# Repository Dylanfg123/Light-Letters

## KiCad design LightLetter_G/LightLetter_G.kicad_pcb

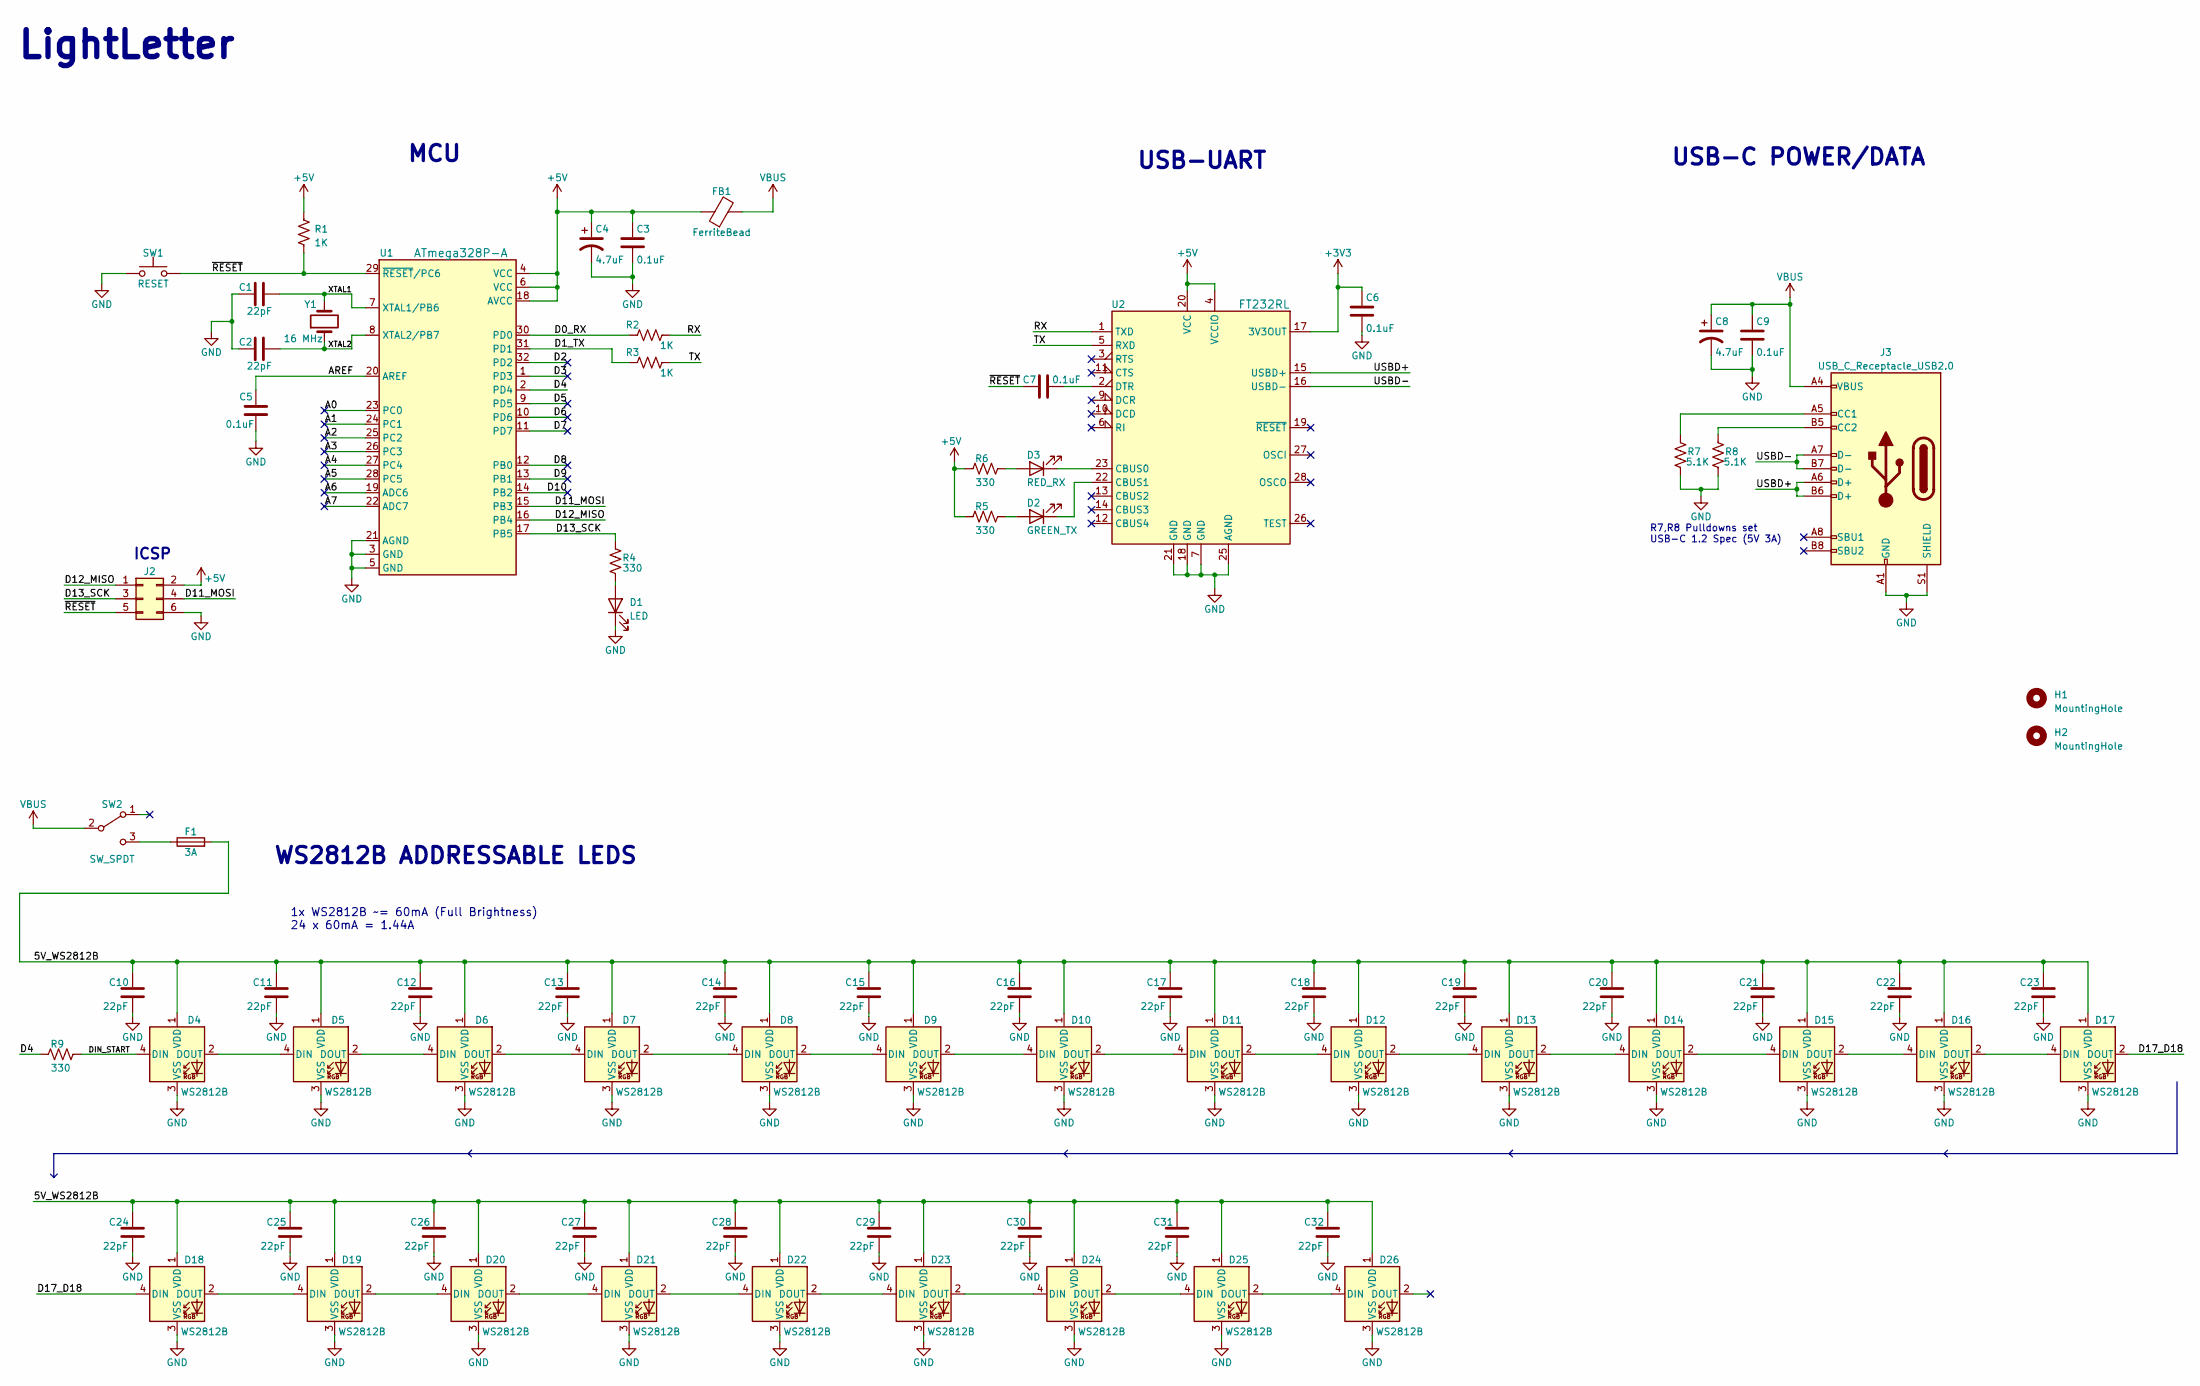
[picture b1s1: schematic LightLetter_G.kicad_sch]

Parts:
C1, C2, C10, C11, C12, C13, C14, C15, C16, C17, C18, C19, C20, C21, C22, C23, C24, C25, C26, C27, C28, C29, C30, C31, C32: 22pF; C_0603_1608Metric; Digikey# 478-KGM15ACG1H220JTCT-ND
C3, C5, C6, C7, C9: 0.1uF; C_0603_1608Metric; Digikey# 478-KGM15BR71H104KMCT-ND
C4, C8: 4.7uF; C_0603_1608Metric; Digikey# 490-12328-1-ND
D1: LED; LED_0603_1608Metric; Digikey# 160-1446-1-ND
D2: GREEN_TX; LED_0603_1608Metric; Digikey# 160-1446-1-ND
D3: RED_RX; LED_0603_1608Metric; Digikey# 160-1447-1-ND
D4, D5, D6, D7, D8, D9, D10, D11, D12, D13, D14, D15, D16, D17, D18, D19, D20, D21, D22, D23, D24, D25, D26: WS2812B; LED_WS2812B_PLCC4_5.0x5.0mm_P3.2mm; Digikey# 1568-COM-16347CT-ND
F1: 3A; Fuse_1206_3216Metric; Digikey# 507-1896-1-ND
FB1: FerriteBead; L_0603_1608Metric; Digikey# 240-2558-1-ND
H1, H2: MountingHole; MountingHole_3.2mm_M3
J2: Conn_02x03_Odd_Even; PinHeader_2x03_P1.27mm_Vertical_SMD; Digikey# SAM14930CT-ND
J3: USB_C_Receptacle_USB2.0; USB_C_Receptacle_GCT_USB4115-03-C; Digikey# 2073-USB4115-03-CCT-ND
R1, R2, R3: 1K; R_0603_1608Metric; Digikey# 311-1.00KHRCT-ND
R4, R5, R6, R9: 330; R_0603_1608Metric; Digikey# 118-CMP0603-FX-3300ELFCT-ND
R7, R8: 5.1K; R_0603_1608Metric; Digikey# RMCF0603FT5K10CT-ND
SW1: RESET; SW_Push_1P1T_NO_6x6mm_H9.5mm; Digikey# CKN10880CT-ND
SW2: SW_SPDT; SW_500ASSP1M6QE; Digikey# EG2483-ND
U1: ATmega328P-A; TQFP-32_7x7mm_P0.8mm; Digikey# ATMEGA328PB-AURCT-ND
U2: FT232RL; SSOP-28_5.3x10.2mm_P0.65mm; Digikey# 768-1007-1-ND
Y1: 16 MHz; XTAL_ABLS7M-16.000MHZ-B-2-T; Digikey# 535-13416-1-ND

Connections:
+3V3: C6.1, U2.17 (3V3OUT)
+5V: C3.1, C4.1, FB1.1, J2.2, R1.1, R5.2, R6.2, U1.4 (VCC), U1.6 (VCC), U1.18 (AVCC), U2.4 (VCCIO), U2.20 (VCC)
/5V_WS2812B: C10.2, C11.2, C12.2, C13.2, C14.2, C15.2, C16.2, C17.2, C18.2, C19.2, C20.2, C21.2, C22.2, C23.2, C24.2, C25.2, C26.2, C27.2, C28.2, C29.2, C30.2, C31.2, C32.2, D4.1 (VDD), D5.1 (VDD), D6.1 (VDD), D7.1 (VDD), D8.1 (VDD), D9.1 (VDD), D10.1 (VDD), D11.1 (VDD), D12.1 (VDD), D13.1 (VDD), D14.1 (VDD), D15.1 (VDD), D16.1 (VDD), D17.1 (VDD), D18.1 (VDD), D19.1 (VDD), D20.1 (VDD), D21.1 (VDD), D22.1 (VDD), D23.1 (VDD), D24.1 (VDD), D25.1 (VDD), D26.1 (VDD), F1.2
/A0: U1.23 (PC0)
/A1: U1.24 (PC1)
/A2: U1.25 (PC2)
/A3: U1.26 (PC3)
/A4: U1.27 (PC4)
/A5: U1.28 (PC5)
/A6: U1.19 (ADC6)
/A7: U1.22 (ADC7)
/AREF: C5.1, U1.20 (AREF)
/D0_RX: R2.1, U1.30 (PD0)
/D1_TX: R3.1, U1.31 (PD1)
/D2: U1.32 (PD2)
/D3: U1.1 (PD3)
/D4: R9.2, U1.2 (PD4)
/D5: U1.9 (PD5)
/D6: U1.10 (PD6)
/D7: U1.11 (PD7)
/D8: U1.12 (PB0)
/D9: U1.13 (PB1)
/D10: U1.14 (PB2)
/D11_MOSI: J2.4, U1.15 (PB3)
/D12_MISO: J2.1, U1.16 (PB4)
/D13_SCK: J2.3, R4.2, U1.17 (PB5)
/D17_D18: D17.2 (DOUT), D18.4 (DIN)
/DIN_START: D4.4 (DIN), R9.1
/RX: R2.2, U2.1 (TXD)
/TX: R3.2, U2.5 (RXD)
/USBD+: J3.A6 (D+), J3.B6 (D+), U2.15 (USBD+)
/USBD-: J3.A7 (D-), J3.B7 (D-), U2.16 (USBD-)
/XTAL1: C1.2, U1.7 (XTAL1/PB6), Y1.2
/XTAL2: C2.2, U1.8 (XTAL2/PB7), Y1.1
/~RESET: C7.1, J2.5, R1.2, SW1.2, U1.29 (~RESET/PC6)
GND: C1.1, C2.1, C3.2, C4.2, C5.2, C6.2, C8.2, C9.2, C10.1, C11.1, C12.1, C13.1, C14.1, C15.1, C16.1, C17.1, C18.1, C19.1, C20.1, C21.1, C22.1, C23.1, C24.1, C25.1, C26.1, C27.1, C28.1, C29.1, C30.1, C31.1, C32.1, D1.1 (K), D4.3 (VSS), D5.3 (VSS), D6.3 (VSS), D7.3 (VSS), D8.3 (VSS), D9.3 (VSS), D10.3 (VSS), D11.3 (VSS), D12.3 (VSS), D13.3 (VSS), D14.3 (VSS), D15.3 (VSS), D16.3 (VSS), D17.3 (VSS), D18.3 (VSS), D19.3 (VSS), D20.3 (VSS), D21.3 (VSS), D22.3 (VSS), D23.3 (VSS), D24.3 (VSS), D25.3 (VSS), D26.3 (VSS), J2.6, J3.A1 (GND), J3.A12 (GND), J3.B1 (GND), J3.B12 (GND), J3.S1 (SHIELD), R7.1, R8.1, SW1.1, U1.3 (GND), U1.5 (GND), U1.21 (AGND), U2.7 (GND), U2.18 (GND), U2.21 (GND), U2.25 (AGND)
unnamed: D1.2 (A), R4.1
unnamed: D2.2 (A), R5.1
unnamed: D2.1 (K), U2.22 (CBUS1)
unnamed: D3.2 (A), R6.1
unnamed: D3.1 (K), U2.23 (CBUS0)
unnamed: D4.2 (DOUT), D5.4 (DIN)
unnamed: D5.2 (DOUT), D6.4 (DIN)
unnamed: D6.2 (DOUT), D7.4 (DIN)
unnamed: D7.2 (DOUT), D8.4 (DIN)
unnamed: D8.2 (DOUT), D9.4 (DIN)
unnamed: D9.2 (DOUT), D10.4 (DIN)
unnamed: D10.2 (DOUT), D11.4 (DIN)
unnamed: D11.2 (DOUT), D12.4 (DIN)
unnamed: D12.2 (DOUT), D13.4 (DIN)
unnamed: D13.2 (DOUT), D14.4 (DIN)
unnamed: D14.2 (DOUT), D15.4 (DIN)
unnamed: D15.2 (DOUT), D16.4 (DIN)
unnamed: D16.2 (DOUT), D17.4 (DIN)
unnamed: D18.2 (DOUT), D19.4 (DIN)
unnamed: D19.2 (DOUT), D20.4 (DIN)
unnamed: D20.2 (DOUT), D21.4 (DIN)
unnamed: D21.2 (DOUT), D22.4 (DIN)
unnamed: D22.2 (DOUT), D23.4 (DIN)
unnamed: D23.2 (DOUT), D24.4 (DIN)
unnamed: D24.2 (DOUT), D25.4 (DIN)
unnamed: D25.2 (DOUT), D26.4 (DIN)
unnamed: J3.A5 (CC1), R7.2
unnamed: J3.B5 (CC2), R8.2
unnamed: F1.1, SW2.3 (C)
unnamed: C7.2, U2.2 (DTR)
VBUS: C8.1, C9.1, FB1.2, J3.A4 (VBUS), J3.A9 (VBUS), J3.B4 (VBUS), J3.B9 (VBUS), SW2.2 (B)

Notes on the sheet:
R7,R8 Pulldowns set USB-C 1.2 Spec (5V 3A)
USB-C POWER/DATA
WS2812B ADDRESSABLE LEDS
MCU
1x WS2812B ~= 60mA (Full Brightness) 24 x 60mA = 1.44A
LightLetter
USB-UART
ICSP

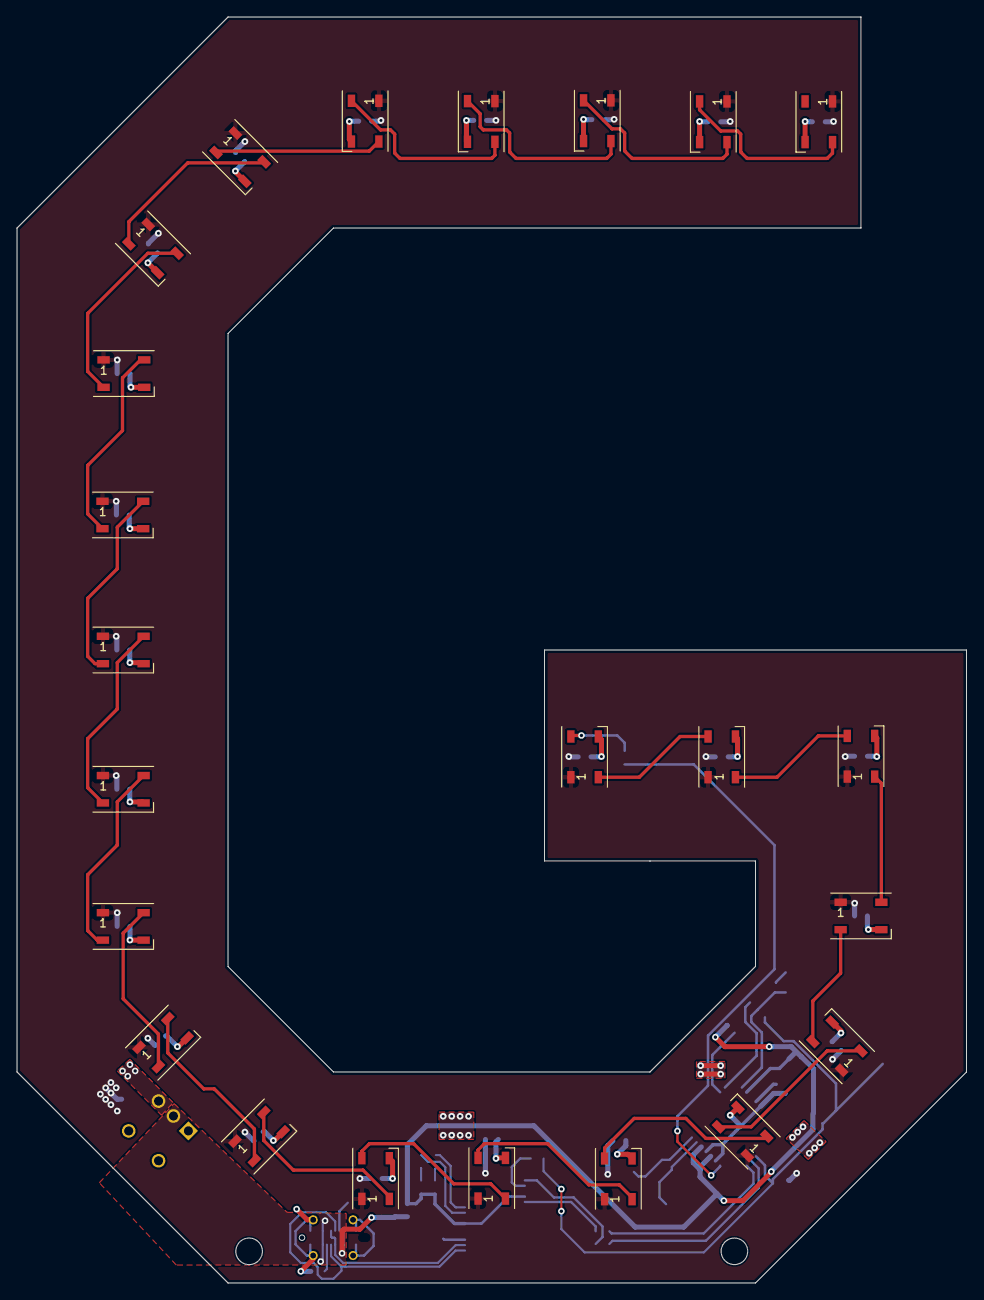
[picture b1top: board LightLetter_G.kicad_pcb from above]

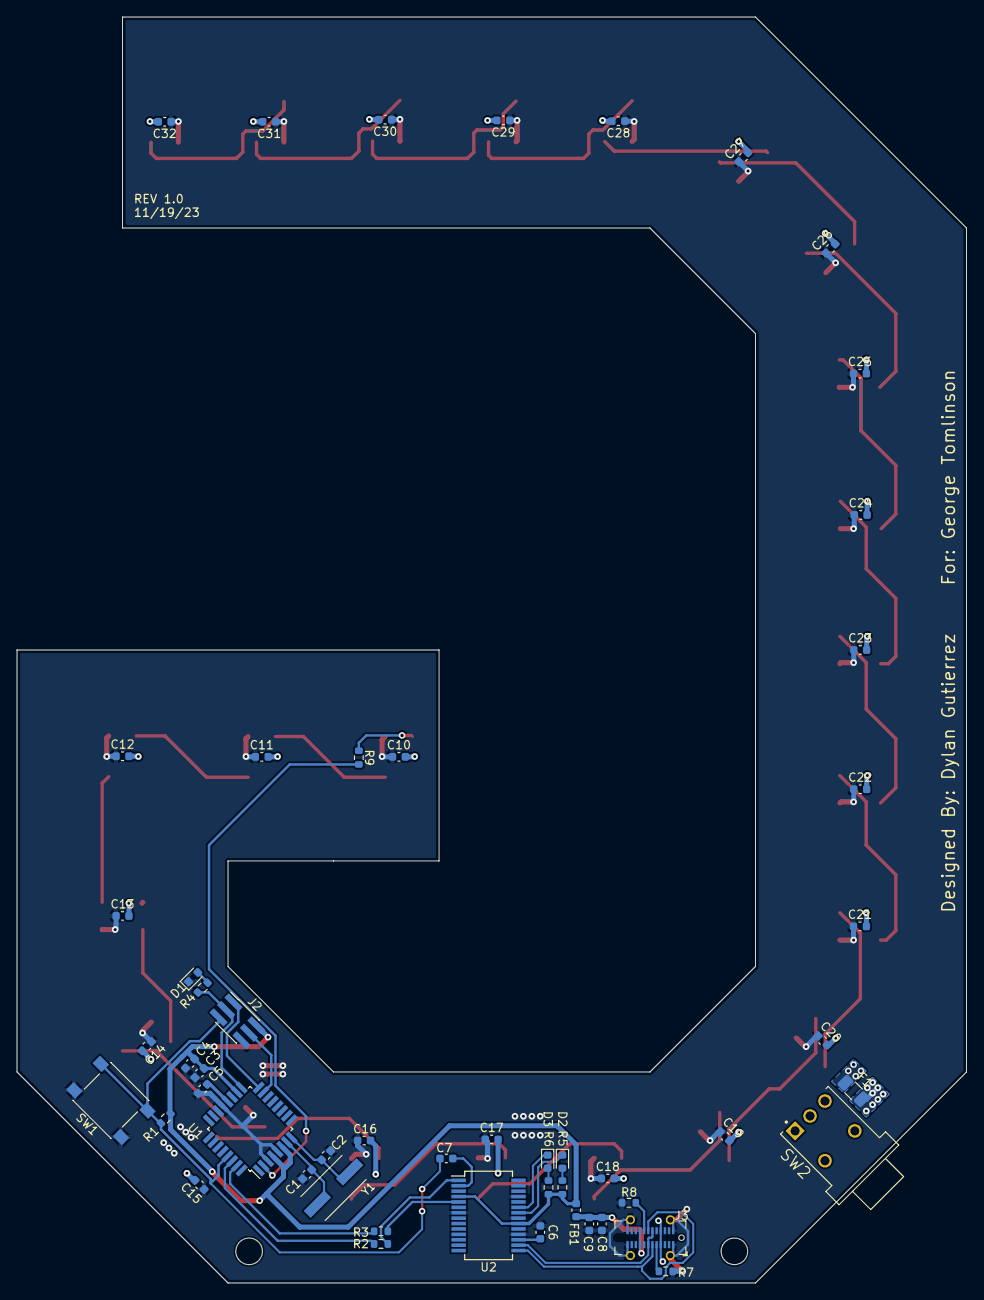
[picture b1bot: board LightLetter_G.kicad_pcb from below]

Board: 2 copper layers, 114.3 x 152.4 mm, 78 parts (53 on the bottom side), 51 nets.

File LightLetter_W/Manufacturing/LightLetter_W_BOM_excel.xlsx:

LightLetter_W_BOM
Item# | References | Value | Footprint | Description | Digikey# | MF | MF# | Quantity
1 | C1, C2, C10, C11, C12, C13, C14, C15, C16, C17, C18, C19, C20, C21, C22, C23, C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 | 22pF | C_0603_1608Metric | CAP CER 22PF 50V C0G/NP0 0603 | 478-KGM15ACG1H220JTCT-ND | KYOCERA AVX | KGM15ACG1H220JT | 25
2 | C3, C5, C6, C7, C9 | 0.1uF | C_0603_1608Metric | CAP CER 0.1UF 50V X7R 0603 | 478-KGM15BR71H104KMCT-ND | KYOCERA AVX | KGM15BR71H104KM | 5
3 | C4, C8 | 4.7uF | C_0603_1608Metric | CAP CER 4.7UF 25V X5R 0603 | 490-12328-1-ND | Murata Electronics | GRT188R61E475KE13D | 2
4 | R4, R5, R6, R9 | 330 | R_0603_1608Metric | RESHIGHPOWER 0603 330R 1% 1/4W T | 118-CMP0603-FX-3300ELFCT-ND | Bourns Inc. | CMP0603-FX-3300ELF | 4
5 | R1, R2, R3 | 1K | R_0603_1608Metric | RES 1K OHM 1% 1/10W 0603 | 311-1.00KHRCT-ND | YAGEO | RC0603FR-071KL | 3
6 | R7, R8 | 5.1K | R_0603_1608Metric | RES 5.1K OHM 1% 1/10W 0603 | RMCF0603FT5K10CT-ND | Stackpole Electronics Inc | RMCF0603FT5K10 | 2
7 | D4, D5, D6, D7, D8, D9, D10, D11, D12, D13, D14, D15, D16, D17, D18, D19, D20, 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 | WS2812B | LED_WS2812B_PLCC4_5.0x5.0mm_P3.2mm | ADDRESS LED RED/GRN/BLUE | 1568-COM-16347CT-ND | SparkFun Electronics | COM-16347 | 23
8 | D1 | LED | LED_0603_1608Metric | LED GREEN CLEAR SMD | 160-1446-1-ND | Lite-On Inc. | LTST-C191KGKT | 1
9 | D2 | GREEN_TX | LED_0603_1608Metric | LED GREEN CLEAR SMD | 160-1446-1-ND | Lite-On Inc. | LTST-C191KGKT | 1
10 | D3 | RED_RX | LED_0603_1608Metric | LED RED CLEAR SMD | 160-1447-1-ND | Lite-On Inc. | LTST-C191KRKT | 1
11 | U1 | ATmega328P-A | TQFP-32_7x7mm_P0.8mm | IC MCU 8BIT 32KB FLASH 32TQFP | ATMEGA328PB-AURCT-ND | Microchip Technology | ATMEGA328PB-AUR | 1
12 | U2 | FT232RL | SSOP-28_5.3x10.2mm_P0.65mm | IC USB FS SERIAL UART 28-SSOP | 768-1007-1-ND | FTDI | FT232RL | 1
13 | Y1 | 16 MHz | XTAL_ABLS7M-16.000MHZ-B-2-T | CRYSTAL 16.0000MHZ 18PF SMD | 535-13416-1-ND | Abracon LLC | ABLS7M-16.000MHZ-B-2-T | 1
14 | F1 | 3A | Fuse_1206_3216Metric | FUSE BRD MNT 3A 63VAC 63VDC 1206 | 507-1896-1-ND | Bel Fuse Inc. | 0685T3000-01 | 1
15 | SW1 | RESET | SW_Push_1P1T_NO_6x6mm_H9.5mm | SWITCH TACTILE SPST-NO 0.05A 12V | CKN10880CT-ND | C&K | PTS645SL43SMTR92 LFS | 1
16 | SW2 | SW_SPDT | SW_500ASSP1M6QE | SWITCH SLIDE SPDT 3A 120V | EG2483-ND | E-Switch | 500ASSP1M6QE | 1
17 | H1, H2 | MountingHole | MountingHole_3.2mm_M3 |  |  |  |  | 2
18 | FB1 | FerriteBead | L_0603_1608Metric | FERRITE BEAD 220 OHM 0603 1LN | 240-2558-1-ND | Laird-Signal Integrity Products | MI0603L221R-10 | 1
19 | J2 | Conn_02x03_Odd_Even | PinHeader_2x03_P1.27mm_Vertical_SMD | CONN HEADER SMD 6POS 1.27MM | SAM14930CT-ND | Samtec Inc. | FTS-103-01-F-DV-TR | 1
20 | J3 | USB_C_Receptacle_USB2.0 | USB_C_Receptacle_GCT_USB4115-03-C | CONN USB3.1 TYPE-C VERT SOCKET | 2073-USB4115-03-CCT-ND | GCT | USB4115-03-C | 1

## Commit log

2023-12-03 Inital commit of rev0 designs for letters 'W' and 'G'
